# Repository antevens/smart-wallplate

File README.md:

# Smart wall plate

Replacement for a single-gang light switch: recessed IKEA BILRESA remote, hidden
emergency rocker, Apollo MSR-2 mmWave presence + SHT45 climate + a push-to-talk
microphone for Home Assistant voice, powered by a Mean Well IRM-03-5 on the wiring board.

Start with `AGENTS.md` (for people too), then `docs/SAFETY.md`. `docs/PRINTING.md` lists the print
jobs in order, `docs/ASSEMBLY.md` what holds each part, `docs/MEASUREMENTS.md` what is measured and
what is still an estimate.

Two variants: **NA** (single-gang Decora box, this page's main renders) and **EU** (round DIN 49073
box, `cad/build123d/eu/`, `pcb/eu/`). Both can run the BILRESA without batteries through a
replacement back cover powered from the plate.

The plate is two printed parts: a **box insert** (all mains/low-voltage barrier
geometry, UL94 V-0 PC-FR) and a **trim plate** (PETG/ASA), for an Elegoo Centauri
Carbon 2.

The house wiring lands on one board: L/N/PE in and out on a WAGO push-in block,
the Marquardt 1802.2504 DPST emergency rocker, and the PSU, all in a 2.5"
single-gang box. The KiCad project is in `pcb/`.

```bash
make system-deps     # once, Ubuntu 24.04 (KiCad 9, headless slicer libs)
make setup           # once (venv + pinned OrcaSlicer)
make cad check       # CAD -> build/, all checks must pass
make print           # OrcaSlicer projects -> print/*.3mf
make pcb             # all boards and flexes: ERC/DRC, STEP, PCBWay packs -> pcb/fab/, pcb/eu/fab/
make eu              # EU variant: CAD, checks, renders
make renders         # docs/renders/*.png
```

Nothing here is certified or code-compliant; see `docs/SAFETY.md`.

## How it is meant to be used

The design assumes every light bulb and device on the switched circuit is a smart
device that turns itself on and off (here IKEA Matter-over-Thread bulbs). The circuit
stays powered; day-to-day control is wireless: the BILRESA remote in the plate, Home
Assistant, the IKEA app, or Alexa / Google / other assistants.

The rocker hidden behind the remote is not the everyday light switch. It is there for
two cases:

- **Controller or cloud down.** When Home Assistant, the IKEA hub or the voice
  assistant is unavailable, turn the rocker off and on again. The bulbs restart and come
  on by themselves at their built-in power-on brightness. This needs each bulb's power-on
  behaviour set to "On" (D-8); check it per bulb.
- **Safety.** Off cuts line and neutral to the fixtures on this circuit (and powers down
  the plate's sensors), for example when a bulb or fixture misbehaves or needs changing.
  It is not a substitute for the breaker: turn the breaker off before working on any
  wiring (`docs/SAFETY.md`).

Voice: the plate's microphone streams to Home Assistant's Assist pipeline only when
listening is started from Home Assistant, for example by an automation on a BILRESA button
(D-29). There is no wake word and no speaker in the plate; replies go to another device.

Plain (non-smart) bulbs on this circuit would just follow the rocker, and the remote,
the sensors and the automations could not control them.

## Renders

### v0.3

Shaded views of the assembly: trim plate (white), box insert (grey), BILRESA
remote (model), Marquardt 1802.2504 rocker (red), wiring board (green, KiCad
model), board posts (orange). Regenerate with `make renders`.

| Front | Remote lifted out |
| --- | --- |
|  |  |

| Half-section | Back, mains side |
| --- | --- |
|  |  |

Exploded: remote, trim plate, box insert, the four board posts that screw into
the insert's bosses (D-28), wiring board (with the rocker, WAGO block and PSU from
the KiCad model).

Sensor flex (D-27, trim and remote hidden): from the MSR-2's rear connector across
the top, down the right channel past the insert, to the SHT45 on its tail.

Power contact: two spring fingers on the flex press on the gold pads of the 5 V jumper's
stiffened end, which sits on a shelf off the insert flange.

5 V power path (insert cut at the pass-through, seen from the right): a single-layer flex
jumper plugs into J2 on the wiring board (Hirose FH12-6S, slide lock), folds once between the
board and the insert (a 40 mm service loop: plug it in with the board held beside the insert,
where the latch can be seen), goes up through the pass-through and out of the flange, and ends
on the shelf under the spring fingers. No wires, no solder joints at assembly.

Face plate lifted off (trim see-through): the flex with the MSR-2, SHT45, mic and spring fingers goes
with the face plate; the 5 V jumper (wiring board J2 -> pass-through -> pad end on the shelf) stays on
the insert side. The fingers on the jumper's pads are the only electrical interface (R9, checked).

Microphone (D-29, push-to-talk voice to Home Assistant): an I²S MEMS microphone under the
flex in the right channel, its port sealed by a gasket ring to a Ø1.0 sound hole in the face
skin. Sections through the sound hole, across and along the channel:

BILRESA model: stadium outline, wheel with its gap ring, three LEDs, side
parting line, and a back that curves from a flat central pad out to the sides.

| Front | Back |
| --- | --- |
|  |  |

Cross-sections: box insert (red, UL94 V-0), trim plate (blue), wiring board
(green), board posts (orange), BILRESA (grey). The dashed line is the wall surface;
the x = -21 cut runs through two posts and their bosses.

### v0.3 wiring board

KiCad renders of `pcb/`. The front faces the plate (rocker, SMD
fuse and MOV, 5 V connector); the back faces the box (WAGO block, PSU). The four
corner holes take the insert's snap posts; they are unplated with no copper round them, and the
PE ring detours round them, so earth continuity never depends on the posts or on vias.

| Front | Back |
| --- | --- |
|  |  |
|  |  |

Without components, so every trace and pour shows:

| Front | Back |
| --- | --- |
|  |  |
|  |  |

### EU variant (concept, D-30, D-36)

A separate design for a round EU flush box (68 mm hole saw, Ø60 inside); `make eu`, `cad/build123d/eu/`,
`pcb/eu/`. The remote sits flush on a V-0 cap over the box; the emergency rocker (Marquardt 1802.2504,
as on the NA plate) under it is hidden until the remote is lifted out. Two boards: a mains board at
the rocker's PCB seat (rocker, two WAGO push-in blocks, fuse, MOV, PSU over a routed relief slot,
5 V island with a header) and a 5 V board just under the cap (pin socket on the header, two spring
pins up through the cap onto gold pads on the sensor flex: nothing soldered, wired or plugged
across). Box values are catalogue placeholders until measured; the stack reaches 43 mm deep (to be
tried in a box).

| Remote in place | Remote lifted: rocker |
| --- | --- |
|  |  |
|  |  |

Face plate lifted off: the spring pins on the 5 V board stand through the cap; the flex's pads on
the pins are the only interface (R9, checked).

| Flex | Power contact through the cap |
| --- | --- |
|  |  |

Section through the spring pins: 5 V board, pins through the cap, flex pads, trim rib behind them.

Mains board: L pours on the front, N pours on the back, the relief slot under the PSU, the 5 V island
with the header; installer labels on the back.

| Mains board, front | Mains board, back |
| --- | --- |
|  |  |
|  |  |

| 5 V board, front | 5 V board, back |
| --- | --- |
|  |  |

### Replacement back cover (D-35, D-40, D-41, D-44, D-45)

Runs the remote without cells. The printed cover snaps onto the remote like the original (clips at
the top and bottom, side ribs, a pry notch) and carries the remote's magnet plate in a clipped pocket
and a flex: two spring fingers poke through windows in its back onto flush gold pads (+5 V, GND) in a
thin pocket-floor insert, a 3.3 V regulator on the flex feeds the remote, and at the terminal end two
more fingers press on the remote's VBAT plate and GND spring. The flex is held by a stiffener and two
heat-staked pegs and, at the end, by lips and hooks on the contact blocks. On NA the floor pads come
from a tongue of the 5 V jumper through the insert above the wall plane; on EU from a tongue of the
sensor flex. No new openings in the mains barrier. Several remote dimensions are still estimates
(`docs/MEASUREMENTS.md`).

| NA, exploded: floor insert, tongue, cover, remote | NA, section on the tongue |
| --- | --- |
|  |  |

| Cover, inside | Cover, back (fingers free) |
| --- | --- |
|  |  |

| Pocket-floor insert in the EU plate | Exploded: remote, cover, floor insert, plate |
| --- | --- |
|  |  |

Cut through a finger: window, finger on the floor pad, ledge, flex. And through the VBAT contact:
the finger on the end section, its dome on the remote's battery plate.

### Sensor flex and 5 V jumper

KiCad projects in `pcb/sensor/` (D-27). The flex is drawn flat: one strip, folded twice at 45°
in the trim. Left to right: CN2 plug (placeholder, not for fabrication yet), the microphone on
its widened section (D-29), the two spring fingers over the jumper's pads, the SHT45 at the tail.

5 V jumper, drawn flat (two layers): FH12 contacts at the left, gold pads for the spring fingers at
the right (+5 V first, GND passing it to the far pad), and the battery-free tongue down to its two
floor pads.

EU sensor flex, drawn flat: CN2 plug, the microphone on its outer side, the two pads under the
spring pins, the battery-free tongue between them (folded 45° on the floor), the SHT45 at the tail.

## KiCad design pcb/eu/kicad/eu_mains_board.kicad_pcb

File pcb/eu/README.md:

# EU mains board and 5 V board (D-30, D-36)

Two boards in the round EU flush box (DIN 49073, Ø60 inside), both hanging from bosses under the
V-0 cap. Generated from `tools/eu_parts.py`, which takes its geometry from
`cad/build123d/eu/params_eu.py`.

## Mains board (`kicad/eu_mains_board.*`)

Round, at the rocker's PCB seat (16.2 mm below its panel face). The rocker breaks line and neutral
of the lights; the PSU is fed from the switched side, so the rocker also turns the sensor off.

| Ref | Part | Side | Nets |
| --- | --- | --- | --- |
| S1 | Marquardt 1802.2504 rocker, DPST, PCB pins, ENEC 12(4) A 250 V~, UL/CSA 15 A | front (through the cap's panel) | 1 L_IN, 1a L_SW, 2 N_IN, 2a N_SW |
| J1 | WAGO 2604-3102, push-in, 2-pole, 4 mm², entry 90° to the board, 400 V III/2; turned 180° from J2 | back | L_SW (pole 1), L_IN (pole 2, upper) |
| J2 | WAGO 2604-3102 (as J1) | back | N_IN (house neutral), N_SW (to the lights) |
| F1 | Schurter UMT 250, T1A 250 VAC | front | L_SW to L_F |
| RV1 | TDK CU4032K275G2, 275 VAC | front | L_F to N_SW |
| PS1 | Traco TMPS 03-105, 5 V 600 mA (IEC/UL 62368-1, IEC 60335-1; OVC II, PD2, reinforced) | back | inputs L_F / N_SW above the slot, outputs +5V / GND below it |
| J3 | Samtec TSM-102-01-L-SV, SMT pin header 1x2, 2.54 mm, 5.84 mm post (no pin tails under the PSU) | front, 5 V island | +5V, GND |
| MH1-MH3 | M2 holes on the cap's long bosses | - | - |

- The lights' current runs in copper pours: L_IN and L_SW on F.Cu (right), N_IN and N_SW on B.Cu
  (left), in above switched, as the rocker's poles; the split between them steps from the rocker's
  poles down to the WAGO block's. WAGO pin rows and body from WAGO's 3D model (8.2 mm apart, levers
  towards the board centre, where the blocks' pins stay 1.0 mm clear of the rocker body on the
  front); blocks at x ±16.6, y 7.5. The PSU feed (L_F, N_SW to F1 / RV1 / PS1) is
  1.0 mm track. Order with 2 oz copper for the load paths (sizing: human review).
- A routed relief slot under the PSU, between its input and output rows, cuts off the 5 V island
  (PSU outputs, J3). Mains copper keeps ≥ 8 mm (clearance and creepage) from it.
- Keep-out areas round the mounting holes: mains copper ≥ 1.0 mm from them.
- No PE on the board: the lights' protective earth is joined in the box (lever connector).
- Installer labels on the back: L IN / L LOAD, N IN / N LOAD at the WAGO blocks, MAINS 230 VAC.

## 5 V board (`kicad/eu_5v_board.*`)

D-shaped, just under the cap, cut below the switch cup; a hole lets the mains board's lower long
boss through. No mains on it.

| Ref | Part | Side | Nets |
| --- | --- | --- | --- |
| J1 | 2.54 mm pin socket 1x2 (8.5 mm), on the mains board's J3 | back | +5V, GND |
| C1 | 22 µF 10 V X5R 1206 | front | +5V to GND |
| P1, P2 | Harwin P70-2200045 SMT spring pins, 2 A | front | GND (P1, upper), +5V (P2) (through the cap onto the flex's pads; order set by the flex's tongue, D-42) |
| MH1, MH2 | M2 holes on the cap's bosses | - | - |

The header posts reach 3.2 mm into the socket (boards 13.8 mm apart; check with the parts).
Nothing is soldered or wired between the boards or across the cap (DESIGN R9, R10).

## Rules

`kicad/eu_mains_board.kicad_dru`: L–N ≥ 3.5 mm, any two different mains nets ≥ 3.5 mm (line / switched
line / fused line, neutral / switched neutral), mains to the 5 V side ≥ 8.0 mm (clearance and
creepage), mains to the PSU's NC pin ≥ 8.0 mm, mains copper ≥ 1.0 mm from the board edge and the
holes; pins of one rated part keep the part's own spacing. The mains pours carry their own 3.5 mm
clearance. Design targets for human review, not a compliance claim.

The net classes come from the project file; `tools/gen_eu.py` rewrites it after every save
(pcbnew's SaveBoard resets it). The single EU PSU board before D-36 was checked without them, so
its isolation was never verified by DRC.

## Regenerate

```bash
make pcb        # or pcb/eu/tools/build.sh
```

PCBWay packs for both boards in `fab/` (`fab/README.md`: order settings and the review checklist).
Order only after the review and a dry fit of the stack in a real box.

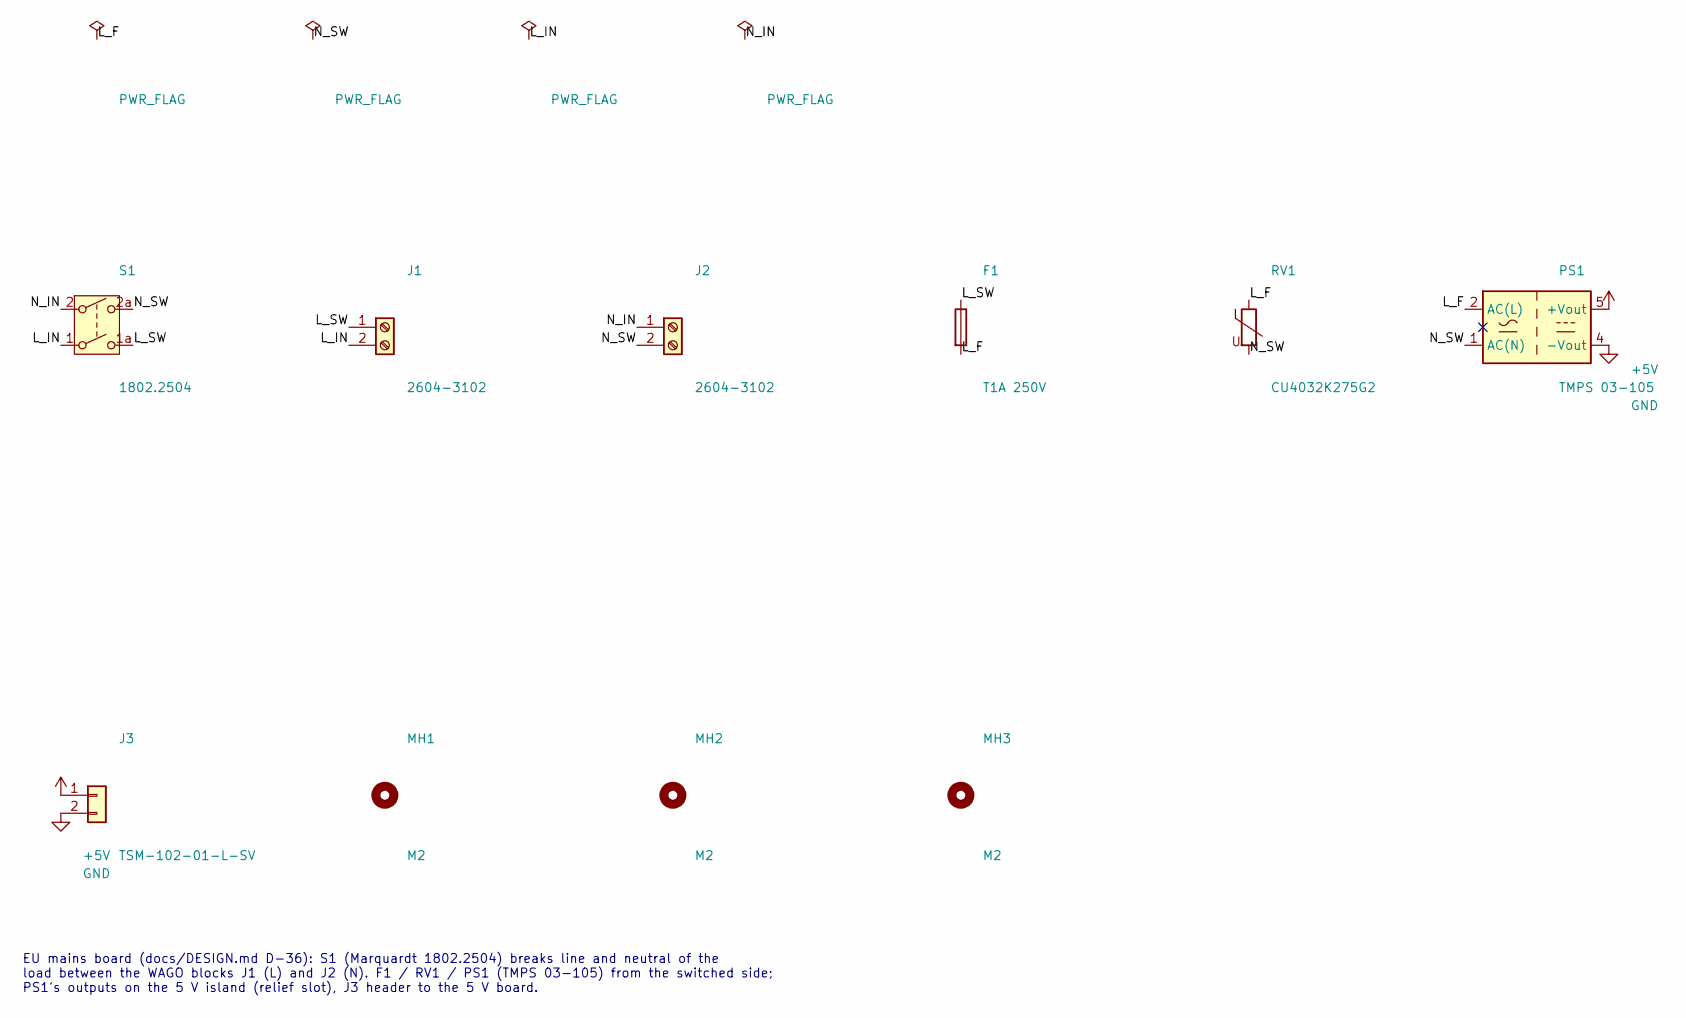
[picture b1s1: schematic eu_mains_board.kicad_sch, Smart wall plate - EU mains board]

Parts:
F1: T1A 250V; Fuse_Schurter_UMT250; MPN 3404.2416.22
J1, J2: 2604-3102; WAGO_2604-3102_1x02_P5.00mm_Vertical; MPN 2604-3102
J3: TSM-102-01-L-SV; PinHeader_1x02_P2.54mm_Vertical_SMD_Pin1Left; MPN TSM-102-01-L-SV
MH1, MH2, MH3: M2; MountingHole_2.2mm_M2
PS1: TMPS 03-105; Converter_ACDC_TRACO_TMPS03_THT; MPN TMPS 03-105
RV1: CU4032K275G2; Varistor_TDK_CU4032; MPN B72660M0271K093
S1: 1802.2504; Marquardt_1802.2504_DPST_PCB; MPN 1802.2504

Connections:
+5V: J3.1, PS1.5 (+Vout)
/L_F: F1.2, PS1.2 (AC(L)), RV1.1
/L_IN: J1.2, S1.1
/L_SW: F1.1, J1.1, S1.1a (2)
/N_IN: J2.1, S1.2 (3)
/N_SW: J2.2, PS1.1 (AC(N)), RV1.2, S1.2a (4)
GND: J3.2, PS1.4 (-Vout)

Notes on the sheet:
EU mains board (docs/DESIGN.md D-36): S1 (Marquardt 1802.2504) breaks line and neutral of the load between the WAGO blocks J1 (L) and J2 (N). F1 / RV1 / PS1 (TMPS 03-105) from the switched side; PS1's outputs on the 5 V island (relief slot), J3 header to the 5 V board.

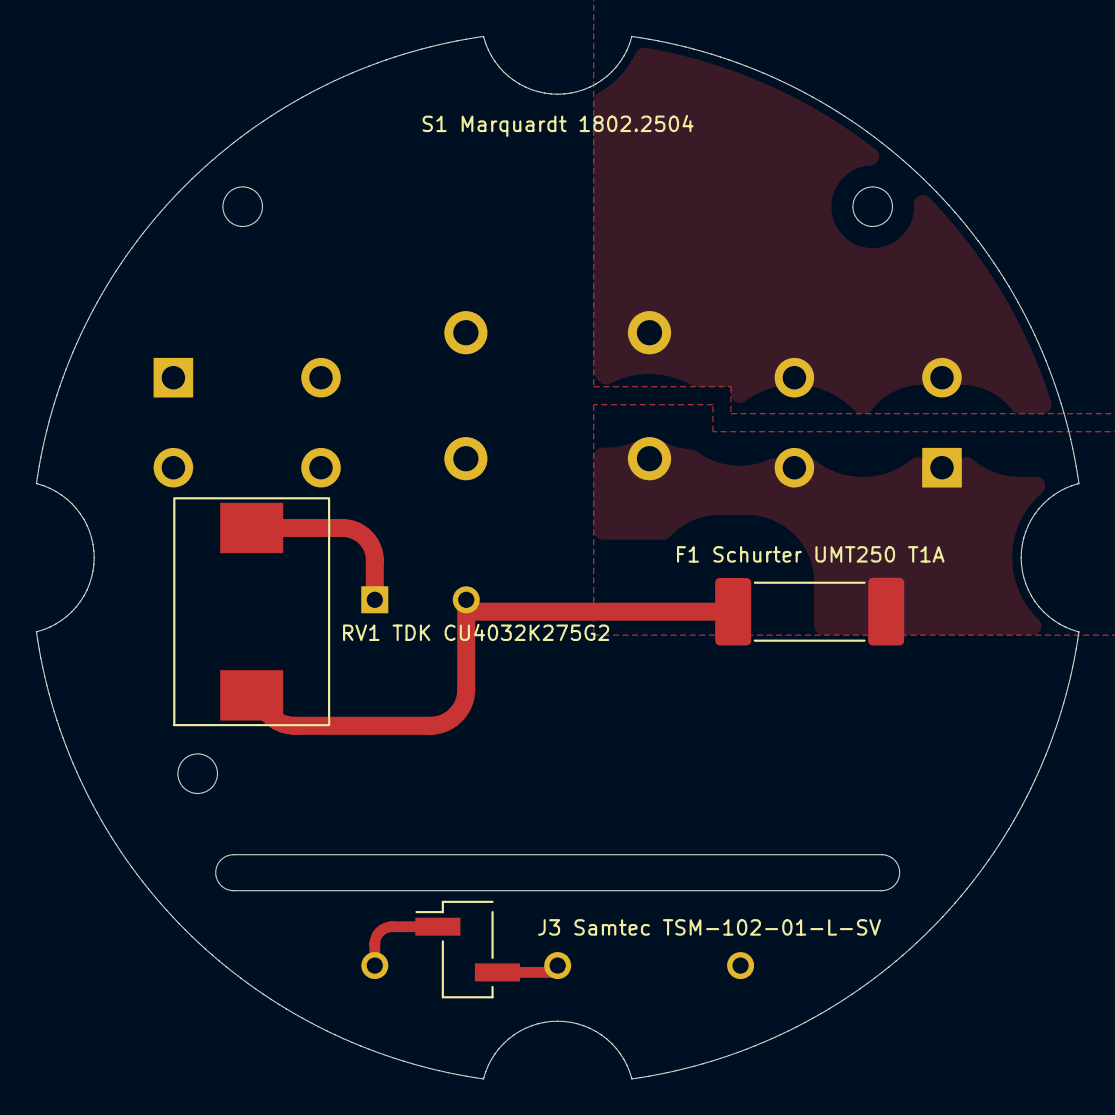
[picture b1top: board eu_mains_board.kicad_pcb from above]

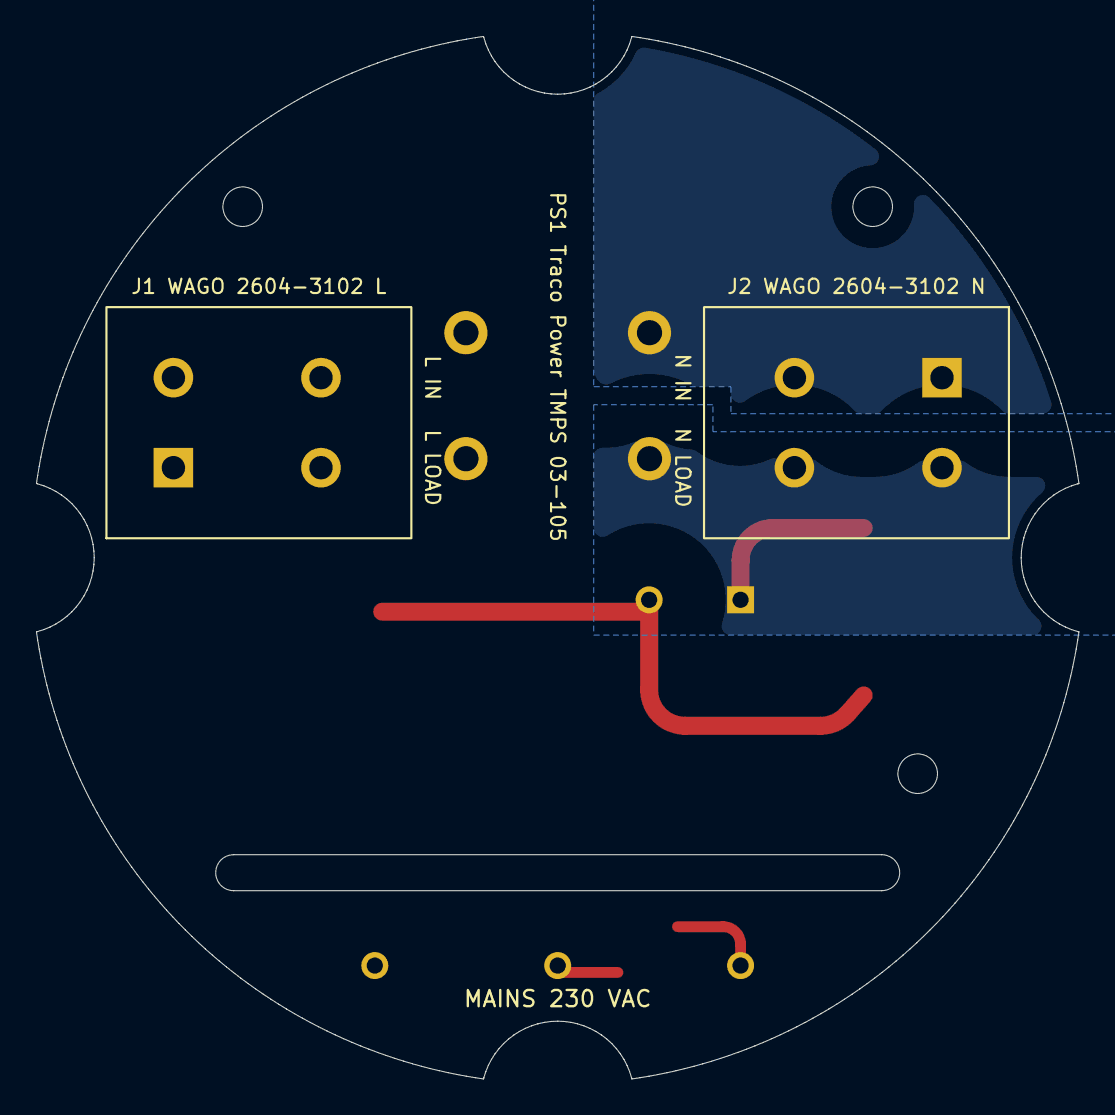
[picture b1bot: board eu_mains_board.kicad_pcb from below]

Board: 2 copper layers, 57.9 x 57.9 mm, 10 parts (3 on the bottom side), 7 nets.

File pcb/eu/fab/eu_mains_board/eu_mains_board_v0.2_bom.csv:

Item,Designator,Qty,Manufacturer,Manufacturer Part Number,Description/Value,Package/Footprint,Layer,Datasheet,Notes
1,S1,0,Marquardt,1802.2504,"1802.2504 - Rocker switch DPST, ENEC 12(4) A 250 V~, UL/CSA 15 A 125-250 VAC, PCB pins: emergency off (line and neutral of the load)",Marquardt_1802.2504_DPST_PCB,Top,"Marquardt drawing 1802.2504 rev g, 2003-09-16 (K-drawing 18022504.03)",Do not fit. Soldered by hand after the rocker is snapped into the printed cap
2,J1,1,WAGO,2604-3102,"2604-3102 - PCB terminal block, push-in, 2-pole, 4 mm2, entry 90 deg to the PCB, 400 V III/2: house line in, switched line to the load",WAGO_2604-3102_1x02_P5.00mm_Vertical,Bottom,https://www.wago.com/global/pcb-terminal-blocks-and-pluggabl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,"Safety-critical, do not substitute. Back (B) side, levers towards the board centre"
3,J2,1,WAGO,2604-3102,"2604-3102 - PCB terminal block, push-in, 2-pole, 4 mm2, entry 90 deg to the PCB, 400 V III/2: house neutral in, switched neutral to the load",WAGO_2604-3102_1x02_P5.00mm_Vertical,Bottom,https://www.wago.com/global/pcb-terminal-blocks-and-pluggabl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,"Safety-critical, do not substitute. Back (B) side, levers towards the board centre"
4,F1,1,Schurter,3404.2416.22,"T1A 250V - SMD fuse UMT 250, time-lag 1 A 250 VAC (TMPS 03 recommended input fuse T1.0 A / 250 V)",Fuse_Schurter_UMT250,Top,https://us.schurter.com/bundles/snceschurter/epim/_ProdPool_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,T1A 250 V per the Traco TMPS 03 datasheet's recommended input fuse - confirm before ordering
5,RV1,1,TDK,B72660M0271K093,"CU4032K275G2 - SMD varistor SIOV-CU4032K275G2K1, 275 VAC",Varistor_TDK_CU4032,Top,https://www.farnell.com/datasheets/2921094.pdf,"Safety-critical, do not substitute without review"
6,PS1,1,Traco Power,TMPS 03-105,"TMPS 03-105 - AC-DC module 85-264 VAC in, 5 V 600 mA, 25.4x25.4x16.3 mm, IEC/UL 62368-1, IEC 60335-1",Converter_ACDC_TRACO_TMPS03_THT,Bottom,https://www.tracopower.com/sites/default/files/products/data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,"Safety-critical, do not substitute. Back (B) side over the routed relief slot, sit flush"
7,J3,1,Samtec,TSM-102-01-L-SV,"TSM-102-01-L-SV - SMT pin header 1x2, 2.54 mm, 5.84 mm post, gold on post: 5 V to the 5 V board's pin socket (5 V island)",PinHeader_1x02_P2.54mm_Vertical_SMD_Pin1Left,Top,https://suddendocs.samtec.com/catalog_english/tsm.pdf,SMT header on the 5 V island (no pin tails under the PSU)

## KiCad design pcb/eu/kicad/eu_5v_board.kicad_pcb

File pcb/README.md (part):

# Wiring board (v0.3)

The single wiring board for the v0.3 plate (docs/DESIGN.md D-24, D-25, D-26). One board
carries the house wiring terminal block, the
emergency rocker that switches line and neutral, and the PSU that feeds the MSR-2.

Spacing values below are design targets for human review. Nothing here is a
compliance claim, and nothing on this board has been checked by a third party.

## Layout

Coordinates are front view in millimetres: X right, Y up toward the rocker, origin at
the board centre. F faces the plate, B faces the box.

- Board: 47 x 72 x 1.6 mm, corner radius 1.5 mm.
- Routed slot: 5 mm wide at X 3.0, from the bottom edge up to Y -10.9, under PS1.
- PE ring on both layers round the AC part, with stitching vias about every 4 mm. Earth
  continuity does not depend on vias or on copper the posts press on: on F.Cu alone, J1.6 ->
  left edge -> round MH1 -> top -> round MH3 -> J1.1 is one piece of copper, and `gen_pcb.py`
  fails the build if it is not (checked with the vias left out). The ring detours round MH1
  and MH3 on the inside; MH2 interrupts the ring's bottom-left corner (the lower part stays joined
  to both arms). B.Cu is a parallel ring joined to J1.6 by the vias.
- PE arms from the ring to J1.6 (left, F) and J1.1 (right, F and B): 10.4 mm wide, flush with
  the outer edges of the pin pair's pads (row distance 8.2 plus the 2.2 mm pad),
  ending square at the pins' centre line so the pads keep the 3.5 mm to the neighbouring
  L / N terminals.
- Pours that compete for copper have fixed priorities (line over neutral), so the fill is
  the same on every rebuild.
- 5 V area: bottom right (X 7 to 19.5, Y -33.5 to -13), GND pour on F.
- Mounting holes for the insert's snap posts (D-28), 2.6 mm, all unplated: MH1 (-21, 33.5),
  MH2 (-21, -33.5), MH3 (21, 24.77), MH4 (21, -33.5). A rule area keeps all copper 2.75 mm
  from each hole on both layers (the post's shoulder and snap head bear on bare laminate).
  Board-only footprints, not in the BOM or centroid. Mains copper keeps 1.0 mm from holes.

## Parts

| Ref | Part | MPN | Side, position | Source |
| --- | --- | --- | --- | --- |
| S1 | Marquardt rocker, DPST, PCB pins | 1802.2504 | F, (0, 19.5), turned 90 degrees | Marquardt drawing 1802.2504 rev g (K-drawing 18022504.03) |
| J1 | WAGO PCB terminal block, 6-pole, 5 mm, lever | 2604-1106 | B, pin 1 at (15.5, 8.1) and (15.5, -0.1) | <https://www.wago.com/global/pcb-terminal-blocks-and-pluggable-connectors/pcb-terminal-block/p/2604-1106> |
| PS1 | Mean Well AC-DC module, 5 V 600 mA | IRM-03-5 | B, under the slot | <https://www.meanwell.com/Upload/PDF/IRM-03/IRM-03-SPEC.PDF> |
| F1 | Schurter UMT 250 SMD fuse, T1A 250 VAC | 3404.2416.22 | F, (-14.6, -23) | <https://us.schurter.com/bundles/snceschurter/epim/_ProdPool_/newDS/en/typ_UMT_250.pdf> |
| RV1 | TDK SMD varistor 275 VAC | B72660M0271K093 (CU4032K275G2) | F, (-5.5, -22) | <https://www.farnell.com/datasheets/2921094.pdf> |
| C1 | Murata MLCC 22 uF 10 V X5R 1206 | GRM31CR61A226KE19L | F, (13, -26) | <https://www.murata.com> |
| J2 | Hirose FH12 FPC connector, 6 contacts, 0.5 mm, slide lock, 5 V out to the flex jumper | FH12-6S-0.5SH(55) | F, (13, -19.5) | <https://www.hirose.com/product/en/products/FH12/FH12-6S-0.5SH(55)/> |

S1 data from the drawing:

- Contacts 1-1a and 2-2a.
- Holes 1.3 (+0.1) mm (drilled 1.4 mm here) on a 10.2 x 7 mm grid as mounted.
- Body 22 x 18.6 mm below the panel, flange 24 x 21 mm.
- PCB seat 16.2 mm below the panel face; rocker 5.3 mm above it.
- Marked ratings: ENEC 12(4) A 250 V~; UL/CSA 15 A 125-250 VAC.
- The drawing is not in the repository.

## Nets

| Net | Class | Connects |
| --- | --- | --- |
| /L_IN | Mains_L | J1.5, S1.1 |
| /L_SW | Mains_L | J1.4, S1.1a, F1.1 |
| /L_F | Mains_L | F1.2, PS1.1 (AC/L), RV1.1 |
| /N_IN | Mains_N | J1.3, S1.2 |
| /N_SW | Mains_N | J1.2, S1.2a, PS1.3 (AC/N), RV1.2 |
| /PE | PE | J1.1, J1.6, PE ring |
| +5V | SELV | PS1.16, C1.1, J2.4–6 |
| GND | SELV | PS1.14, C1.2, J2.1–3 |

S1 pin positions (front view): L_IN (-5.1, 19.5), L_SW (-5.1, 26.5), N_IN (5.1, 19.5),
N_SW (5.1, 26.5). Pins 1 / 2 lie on the body's centre line, 1a / 2a 7 mm off it (drawing
1802.2504 rev g), so the body is centred on the in pins.

Load current path:

- Line: J1.5 to S1.1 on F, then S1.1a to J1.4 on B. The B path runs down under J1 and
  up the left edge.
- Neutral: J1.3 to S1.2 on F, then S1.2a to J1.2 on B. The B path runs up the right side.

## Rules

The rules are in `kicad/wiring_board.kicad_dru`, written by `tools/gen_project.py`.

- L to N: 3.5 mm.
- L_IN to L_SW and L_F: 3.5 mm.
- N_IN to N_SW: 3.5 mm.
- Mains to PE: 3.5 mm.
- Mains to SELV: 8.0 mm clearance and creepage, with the routed slot.
- Mains to the PSU NC pin: 8.0 mm.
- Mains copper to board edge: 1.0 mm; other copper 0.5 mm.
- Pads of one footprint keep the part's own spacing. This is the exception for
  certified parts.

Creepage is checked only for mains to SELV. On this flat board the surface path
between copper on one layer is never shorter than the straight gap, so the 3.5 mm
targets are checked as clearance. KiCad evaluates creepage rules without the
footprint, so a per-part creepage exception cannot be written.

## Status

Done:

- Generators for the libraries, the project and rules, the schematic, the board and the
  3D envelopes.
- Placement, outline and slot, PE ring with stitching vias, pours, tracks and silkscreen.
- All nets routed.
- ERC: 0 errors, 0 warnings.
- DRC (`--severity-all --schematic-parity`): 0 violations, 0 unconnected, 0 parity issues.
- STEP model in `build/wiring_board.step`; PCBWay order pack in `fab/`; renders in
  `docs/renders/wiring_board_*.png` (`make renders`).

Open:

- Meter-check the S1 pin numbering on a sample. The drawing's side view labels the
  pins 1a / 1 / 1b.
- Check the J1 pin rows on a part. They come from WAGO's 3D model (rows y 8.1 and -0.1,
  8.2 apart, D-37).
- Thermal review of the 15 A paths. The 3.5 mm targets to the neighbouring J1 pads (round,
  2.2 mm, 5 mm pitch) leave 1.6 to 1.8 mm of pour beside each pad (N_SW 1.3 mm, beside
  the PE arm) over the 2 to 3 mm where the pours leave J1. Options are 2 oz copper, or
  different targets between in and switched terminals of one pole.
- S1's body sits on the front over J1's first pin row: pad edge 1.0 mm from the body
  outline (`PAD_BODY_GAP`, checked by `make check` for every through-hole pad against the
  bodies on the other side). J1's levers overhang the S1 pins 13.9 mm or more above the
  board.
- F1 rating (T1A) is a designer's choice. Its 200 A breaking capacity at 250 VAC
  needs review against the branch circuit's prospective fault current.
- RV1 pad gap: the datasheet's D = 10.1 mm does not match B + C + B; the larger gap
  is used.
- C1 is a generic part; any 22 uF 10 V X5R 1206 fits.

## Silkscreen labels and 3D models (all boards)

Every part carries a silkscreen label with its reference and maker / model (value and size for
generic passives; net names on bare contact pads), on the side it is mounted, placed by
`tools/kigen.py` (`place_labels`): next to the part, clear of pads, other silkscreen, other parts'
courtyards and the board outline (slots included). On a single-layer flex with no room on the
copper side the label goes on the bare back. ERC / DRC (all severities) check the result.

3D models come from `tools/gen_3d.py` into each project's `kicad/3d/`: a vendor STEP from
`scratch/3d/` when present (moved into footprint coordinates by its entry), otherwise an envelope
from the datasheet dimensions. Vendor files stay in the git-ignored `scratch/` (their terms).

| Model | Source now | Vendor model |
| --- | --- | --- |
| Traco TMPS 03 | vendor (tracopower.com, 3D drawings; pins checked against the pads) | in use |
| Mean Well IRM-03, Hirose FH12-6S, Samtec TSM (EU J3), 0402 / 1206 passives | KiCad library | in use |
| Schurter UMT 250 | envelope | <https://www.schurter.com/en/datasheet/UMT%20250> |
| TDK SIOV CU4032K275G2 (B72660M0271K093) | envelope | <https://product.tdk.com/en/search/sensor/protect/varistor/info?part_no=B72660M0271K093> |
| WAGO 2604-3102 | vendor (wago.com, CADENAS; pins checked against the pads) | in use |
| WAGO 2604-1106 | vendor (wago.com, CADENAS; pins checked against the pads) | in use |
| Marquardt 1802.2504 | vendor 1802.1108 housing (Marquardt LIB_1802.1108; same 1802 flange, rocker, body) on the 1802.2504 underside from its drawing (body to 11.7, pin stems to the 16.2 seat, 0.8 pins; pins checked against the pads) | 1802.2504 itself: on request from Marquardt |
| Harwin P70-2200045 | envelope | <https://www.harwin.com/products/P70-2200045/> |
| Harwin S7081-42R | envelope (shape from the drawing) | <https://www.harwin.com/products/S7081-42R/> |
| PUI DMM-4026-B-I2S-R | envelope | <https://puiaudio.com/product/microphones/dmm-4026-b-i2s-r> |
| Sensirion SHT45 (DFN-4) | envelope | <https://sensirion.com/products/catalog/SHT45> |

To use a vendor model: put its STEP in `scratch/3d/`, add the file name and its transform to the
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
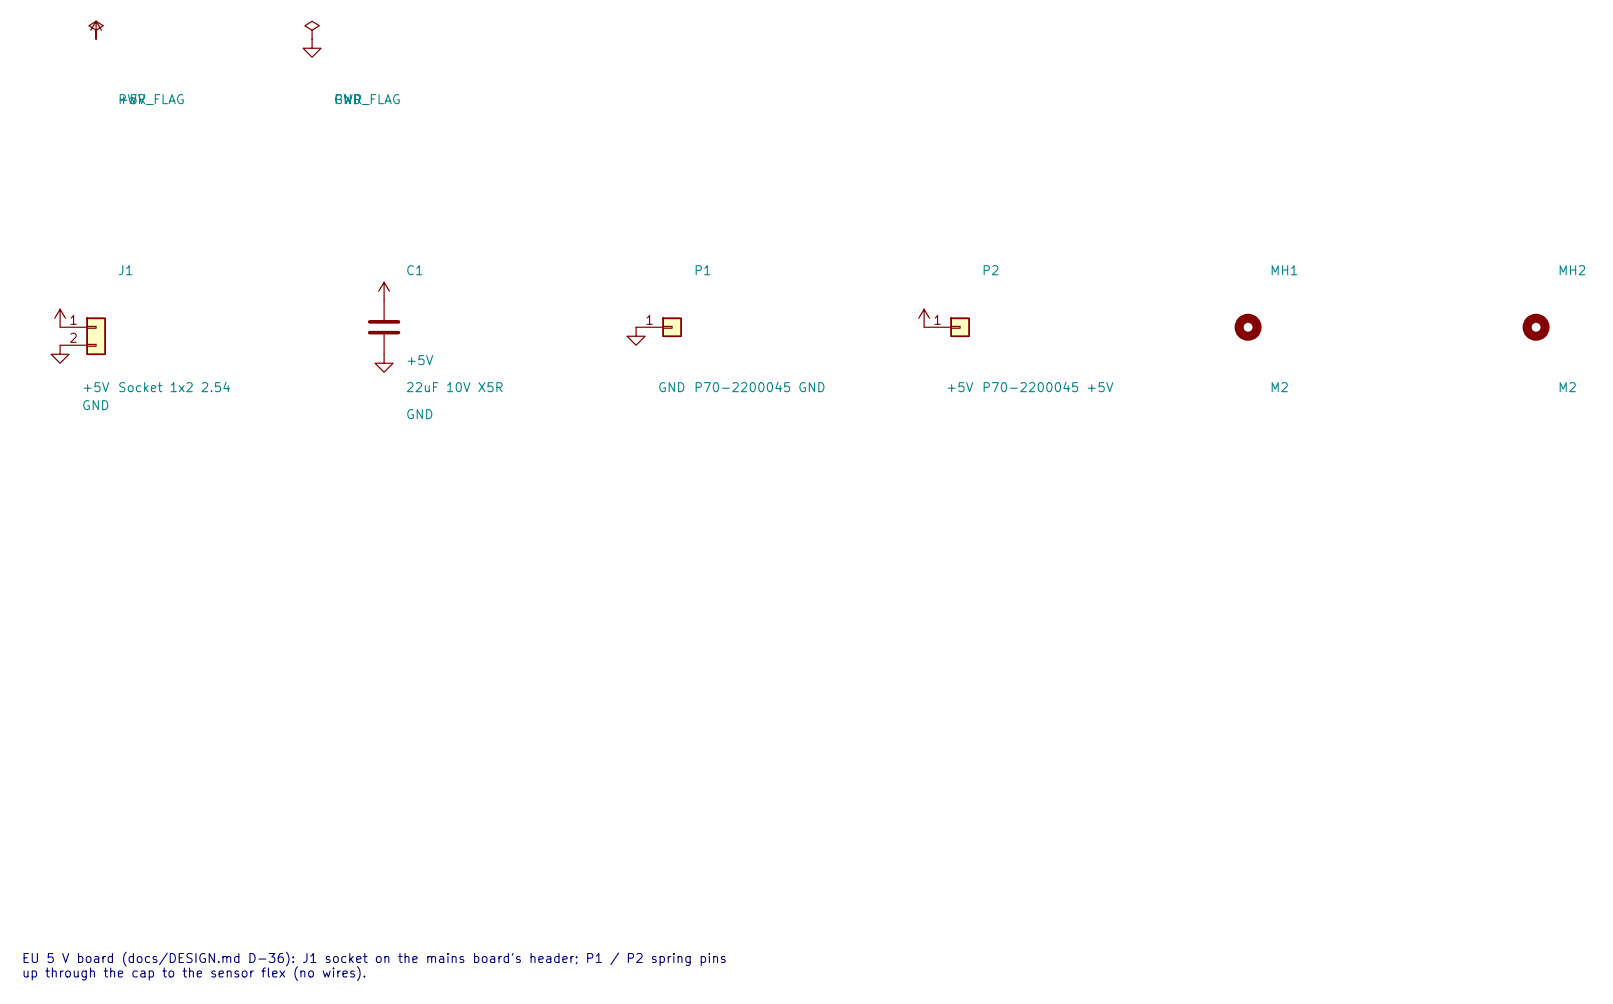
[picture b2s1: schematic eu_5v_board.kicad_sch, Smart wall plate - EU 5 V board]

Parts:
C1: 22uF 10V X5R; C_1206_3216Metric; MPN GRM31CR61A226KE19L
J1: Socket 1x2 2.54; PinSocket_1x02_P2.54mm_Vertical; MPN SSW-102-01-L-S
MH1, MH2: M2; MountingHole_2.2mm_M2
P1: P70-2200045 GND; Harwin_P70-2200045; MPN P70-2200045
P2: P70-2200045 +5V; Harwin_P70-2200045; MPN P70-2200045

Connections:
+5V: C1.1, J1.1, P2.1
GND: C1.2, J1.2, P1.1

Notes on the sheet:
EU 5 V board (docs/DESIGN.md D-36): J1 socket on the mains board's header; P1 / P2 spring pins up through the cap to the sensor flex (no wires).

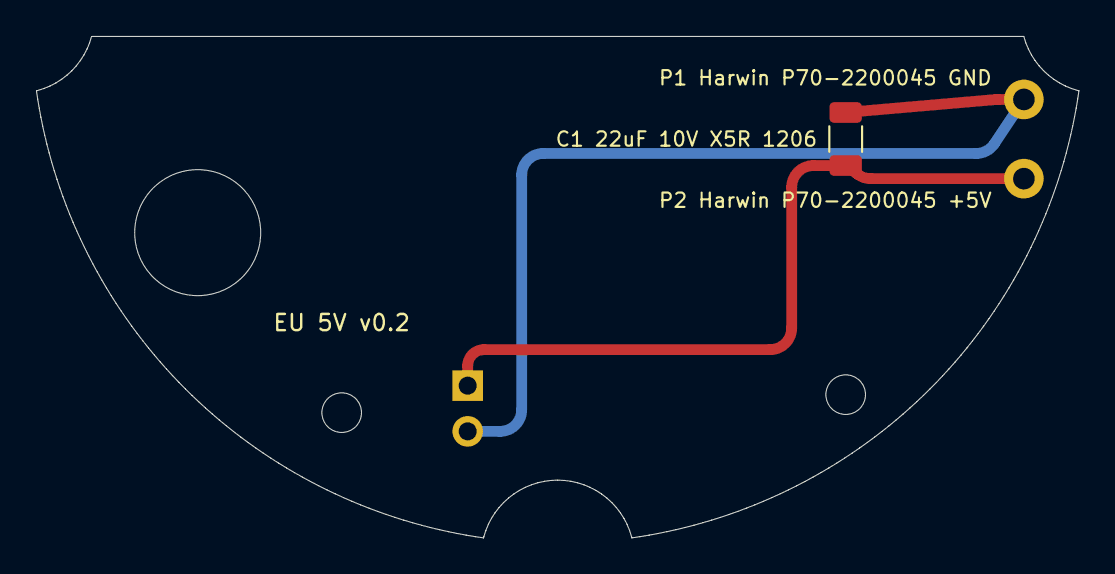
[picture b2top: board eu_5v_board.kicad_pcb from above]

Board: 2 copper layers, 57.9 x 27.9 mm, 6 parts (1 on the bottom side), 2 nets.

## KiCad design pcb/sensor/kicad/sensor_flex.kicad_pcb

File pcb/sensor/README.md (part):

# Sensor flex and 5 V jumper (D-27, D-29)

Two flex circuits on the 5 V side, generated from `tools/sensor_parts.py`, which takes its
geometry from `cad/build123d/params.py` (the same routes and shelf as the CAD models in
`cad/build123d/sensor_flex.py` and `cad/build123d/jumper.py`).

Nothing here touches mains. Both boards are low-voltage only.

## Sensor flex

Single copper layer (F.Cu; KiCad keeps an empty B.Cu), polyimide, 0.12 mm, FR4 stiffeners.

In the trim the flex runs from the MSR-2 across the top, down the right channel and along the
bottom to the SHT45. Each of the two 90° corners is a 45° fold, which turns the strip over, so
in the flat it is one straight strip about 195 mm long with every part on the copper side:

- J1: mating plug for the MSR-2's rear connector CN2 (faces the MSR-2).
- J2, J3: Harwin S7081-42R spring fingers, +5 V and GND (face the jumper's pad end).
- U1: Sensirion SHT45 with C1 (100 nF) on the tail (face the trim's vents).
- MK1: PUI Audio DMM-4026-B-I2S-R I²S microphone with C2 (100 nF) and R1 (100 kΩ SD pull-down),
  in the right channel above the fingers, port towards the face skin (D-29).

The fold lines are on `Cmts.User`, the stiffeners (behind J1, behind J2/J3 and behind MK1) on
`User.1`.

Between the plug end and the strip the flex tapers over 10 mm (`FLEX_NECK_L`), shallow enough
for the ten lanes to run in parallel; the MSR-2 bay frame's notch is sized from that outline.

Over the finger section the flex widens: towards the flange over the finger pads, and into a
1 mm recess in the trim's side wall for the four tracks that pass the pads.

Above the finger section the flex widens towards the flange (to 4.4 mm from the centre line,
room y 38–46) for the microphone. Its pins face the plug, the port end the fingers; the GND ring
(soldered all round, it seals the port) surrounds a Ø0.5 hole through flex and stiffener. On the
skin side an adhesive gasket ring (OD 2.6, ID 1.0, 0.15 mm) seals the stiffener to the face
skin around the Ø1.0 sound hole.

Nets: +5V (fingers to CN2), GND, +3V3 (CN2 to the SHT45), SDA = IO1, SCL = IO0 (MSR-2 I²C
bus; SHT45 at 0x44), I2S_SCK = IO4, I2S_WS = IO6, I2S_SD = IO7, MIC_3V3 and MIC_GND (the
microphone's own CN2 contacts, joined to +3V3 and GND on the MSR-2, so its lanes cross no
others).

## Microphone firmware (D-29)

ESPHome on the MSR-2, push-to-talk: Home Assistant starts listening (for example from a BILRESA
button automation calling the action) and the voice pipeline ends it on silence. Untested
starting point:

```yaml
i2s_audio:
  - id: i2s_mic_bus
    i2s_lrclk_pin: GPIO6
    i2s_bclk_pin: GPIO4

microphone:
  - platform: i2s_audio
    id: plate_mic
    i2s_audio_id: i2s_mic_bus
    adc_type: external
    i2s_din_pin: GPIO7
    channel: left              # LR tied to GND
    bits_per_sample: 32bit     # 24-bit data in a 32-bit word
    sample_rate: 48000         # BCLK 3.072 MHz; the mic sleeps below 2.048 MHz

voice_assistant:
  microphone: plate_mic

api:
  actions:
    - action: start_listening
      then:
        - voice_assistant.start:
    - action: stop_listening
      then:
        - voice_assistant.stop:
```

Open: whether the pipeline accepts 48 kHz from this microphone on the C3 or needs 32 kHz, and
the C3's RAM / CPU headroom next to the radar, Wi-Fi and BLE.

**Not ready to fabricate.** J1's footprint (0.4 mm, 2 x 15) and its contact map are
placeholders: CN2's part and pin map are not confirmed (D-27, `docs/MEASUREMENTS.md`). The map
in `CN2_MAP` only keeps the single-layer fan-out from crossing. `tools/build.sh` writes no flex
fab files while `CN2_CONFIRMED` is false.

## 5 V jumper

Two copper layers, polyimide, 0.2 mm (design value, confirm with the PCBWay stack-up), 156 mm long
in the flat (`params.jumper_length()` plus the two ends) plus the battery-free tongue (D-41). It replaces the 5 V lead and the target board: nothing on the 5 V path is wired or
soldered at assembly (DESIGN R9).

- J1: six exposed contacts at 0.5 mm pitch on a stiffened end (3.5 wide, 0.3 thick in total,
  `JUMPER_END`, MEASURE: check against Hirose's FPC drawing for the FH12-6S) that plugs into J2
  of the wiring board (Hirose FH12-6S-0.5SH, slide lock). Contacts 1–3 GND, 4–6 +5V, as on J2.
  Which face carries the contacts against J2's bottom contacts is to be checked on a sample.
- Run: 3.0 mm wide, +5V and GND tracks 0.5 mm (the MSR-2 draws < 0.2 A).
- TP1, TP2: gold pads (4.5 × 1.8) on the stiffened pad end (0.6 mm in total, FR4), which lies
  on the insert's shelf under the spring fingers: +5 V nearer the run, GND at the far end, its
  track passing the +5 V pad on the wall side.

Assembly: plug the connector end into J2 with the wiring board held beside the insert, where
the latch can be seen; thread the end up through the pass-through (3.5 mm end, Ø4.5 hole); fit
the board; the 40 mm service loop (`JUMPER_SERVICE`) folds between board and insert; the pad end
lies on the shelf (adhesive on its stiffener).

- Battery-free tongue (D-41): leaves the pad end's inner edge between TP1 and TP2, through a tunnel in
  the insert flange (above the wall plane), down a groove in the pocket wall and the wall into the NA
  floor insert's recess (two 90° bends, copper stays up), then a run, a down strip clear of the switch
  well's opening and the pad strip: TP3 / TP4, 7 × 4 mm gold pads (+5V, GND) under the back cover's
  fingers. GND stays on F.Cu off the edge lane; +5V leaves TP1 through a via and passes under it on
  B.Cu, which is why the jumper has two layers. Drawn flat from `sensor_parts.TONGUE_PTS`.

## Back cover flex

Single copper layer, polyimide, for the replacement back cover that powers a BILRESA E2490
without cells (`cad/build123d/backcover.py`, DESIGN D-35). Drawn flat, seen from the copper side.

- J1, J2: Harwin S7081-42R spring fingers (+3V3, GND) on the pad section, which lies copper down
  on a ledge in the cover; the fingers reach through windows onto the plate's flush floor pads
  (working height 2.0 mm).
- A 2.6 mm run (through a slot under the GND contact block) to the terminal end; one 90° bend
  (copper outside).
- J1 takes +5 V from the floor (D-41); U1 TI TLV75533PDBVR (3.3 V, SOT-23-5) with C3 / C4 1 µF on
  the section below the fingers, copper down in a recess in the cover (0.4 mm wall left), feeds VBAT.
- J3, J4: Harwin S7081-42R spring fingers (VBAT, GND) on the end section, on the cell axes, long
  axis vertical with the bend end up (the battery contacts ride down the arm's ramp as the cover
  goes on), on a 0.4 mm FR4 stiffener (back side). The end section stands 2.0 mm (the fingers'
  working height) in from the cell end plane: J3 presses the remote's fixed VBAT plate, J4 its GND
  leaf spring (finger and leaf share the travel). Between them only a band passes under the
  remote's PCB strip.

Not ready to fabricate: the positions come from the FCC internal photos (REF) or are MEASURE;
`tools/build.sh` writes no `fab/cover_flex/` while `COVER_CONFIRMED` is false.

## EU sensor flex (`kicad/eu_sensor_flex.*`, D-30, D-42)

Single copper layer, the NA topology on the EU route (`cad/build123d/eu/sensor_eu.py`), drawn flat by
`tools/eu_flex_parts.py` (X developed along the strip through the dip, Y inwards).

- J1: CN2 mate (placeholder footprint and contact map, as on the NA flex). GND comes out on two
  contacts: GND (pin pad, tongue) and GND_SHT (the SHT45), joined on the MSR-2; MIC_3V3 / MIC_GND as
  on the NA flex.
- MK1 on the strip's outer side (mic section widened outwards): WS / SCK enter the inner pad column
  from above, SD from below through the gap with R1 (100k to MIC_GND) before the body; MIC_GND /
  MIC_3V3 run under the outer column with C2 across them; GND on to the port ring.
- TP1 / TP2: Ø2.4 pads under the 5 V board's spring pins, GND first (P1), then +5V (P2); +5V and
  the SHT45 lanes step under TP1.
- Battery-free tongue (D-41): off the pad section's inner edge between TP1 and TP2 (GND from TP1,
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
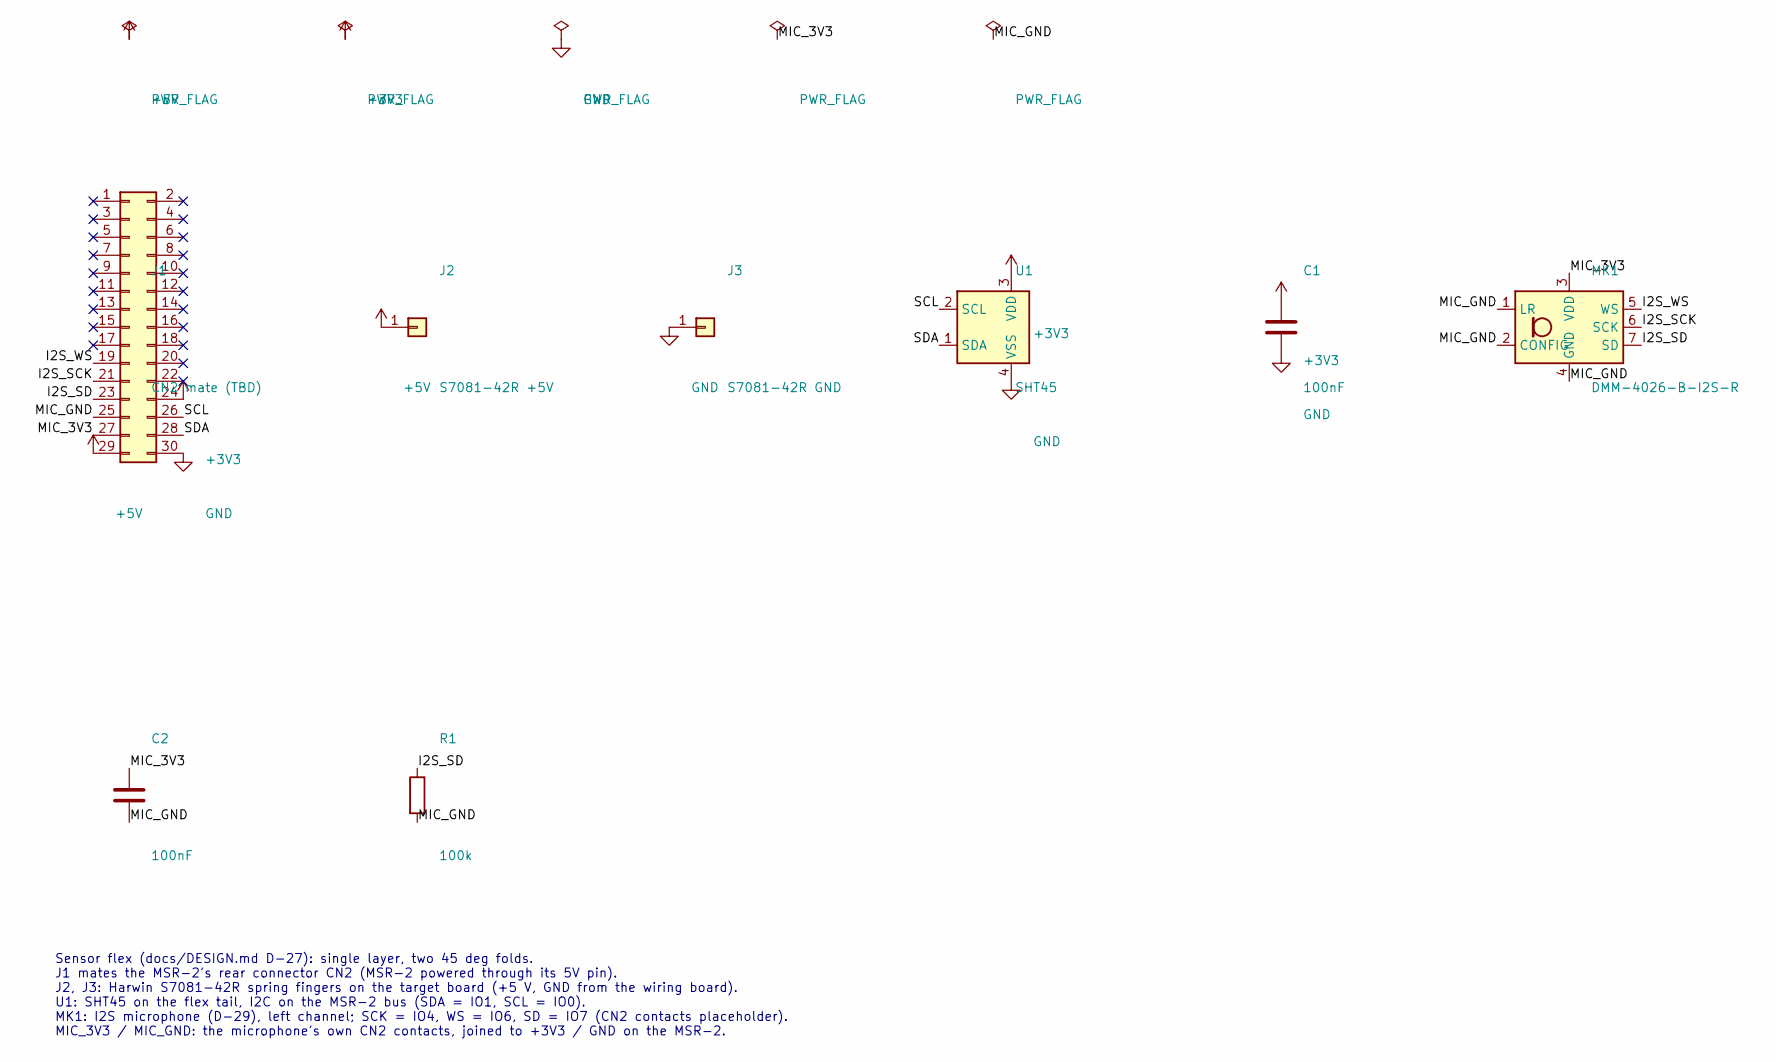
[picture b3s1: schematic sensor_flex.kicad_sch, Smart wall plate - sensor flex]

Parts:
C1, C2: 100nF; C_0402_1005Metric; MPN 0402 X7R 100 nF 16 V
J1: CN2 mate (TBD); B2B_0.4mm_2x15_PLACEHOLDER; MPN TBD
J2: S7081-42R +5V; Harwin_S7081-42R; MPN S7081-42R
J3: S7081-42R GND; Harwin_S7081-42R; MPN S7081-42R
MK1: DMM-4026-B-I2S-R; PUI_DMM-4026-B-I2S_4x3mm; MPN DMM-4026-B-I2S-R
R1: 100k; R_0402_1005Metric; MPN 0402 1% 100 kOhm
U1: SHT45; Sensirion_DFN-4_1.5x1.5mm_P0.8mm_SHT4x_NoCentralPad; MPN SHT45-AD1B-R2

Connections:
+3V3: C1.1, J1.24, U1.3 (VDD)
+5V: J1.29, J2.1
/I2S_SCK: J1.21, MK1.6 (SCK)
/I2S_SD: J1.23, MK1.7 (SD), R1.1
/I2S_WS: J1.19, MK1.5 (WS)
/MIC_3V3: C2.1, J1.27, MK1.3 (VDD)
/MIC_GND: C2.2, J1.25, MK1.1 (LR), MK1.2 (CONFIG), MK1.4 (GND), R1.2
/SCL: J1.26, U1.2 (SCL)
/SDA: J1.28, U1.1 (SDA)
GND: C1.2, J1.30, J3.1, U1.4 (VSS)

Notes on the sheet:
Sensor flex (docs/DESIGN.md D-27): single layer, two 45 deg folds. J1 mates the MSR-2's rear connector CN2 (MSR-2 powered through its 5V pin). J2, J3: Harwin S7081-42R spring fingers on the target board (+5 V, GND from the wiring board). U1: SHT45 on the flex tail, I2C on the MSR-2 bus (SDA = IO1, 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

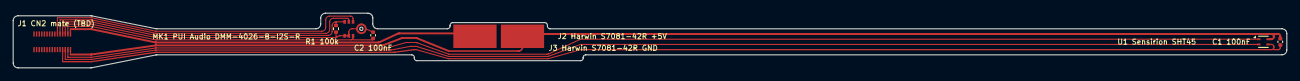
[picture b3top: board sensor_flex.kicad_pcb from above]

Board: 2 copper layers, 195.7 x 8.4 mm, 8 parts (0 on the bottom side), 10 nets.

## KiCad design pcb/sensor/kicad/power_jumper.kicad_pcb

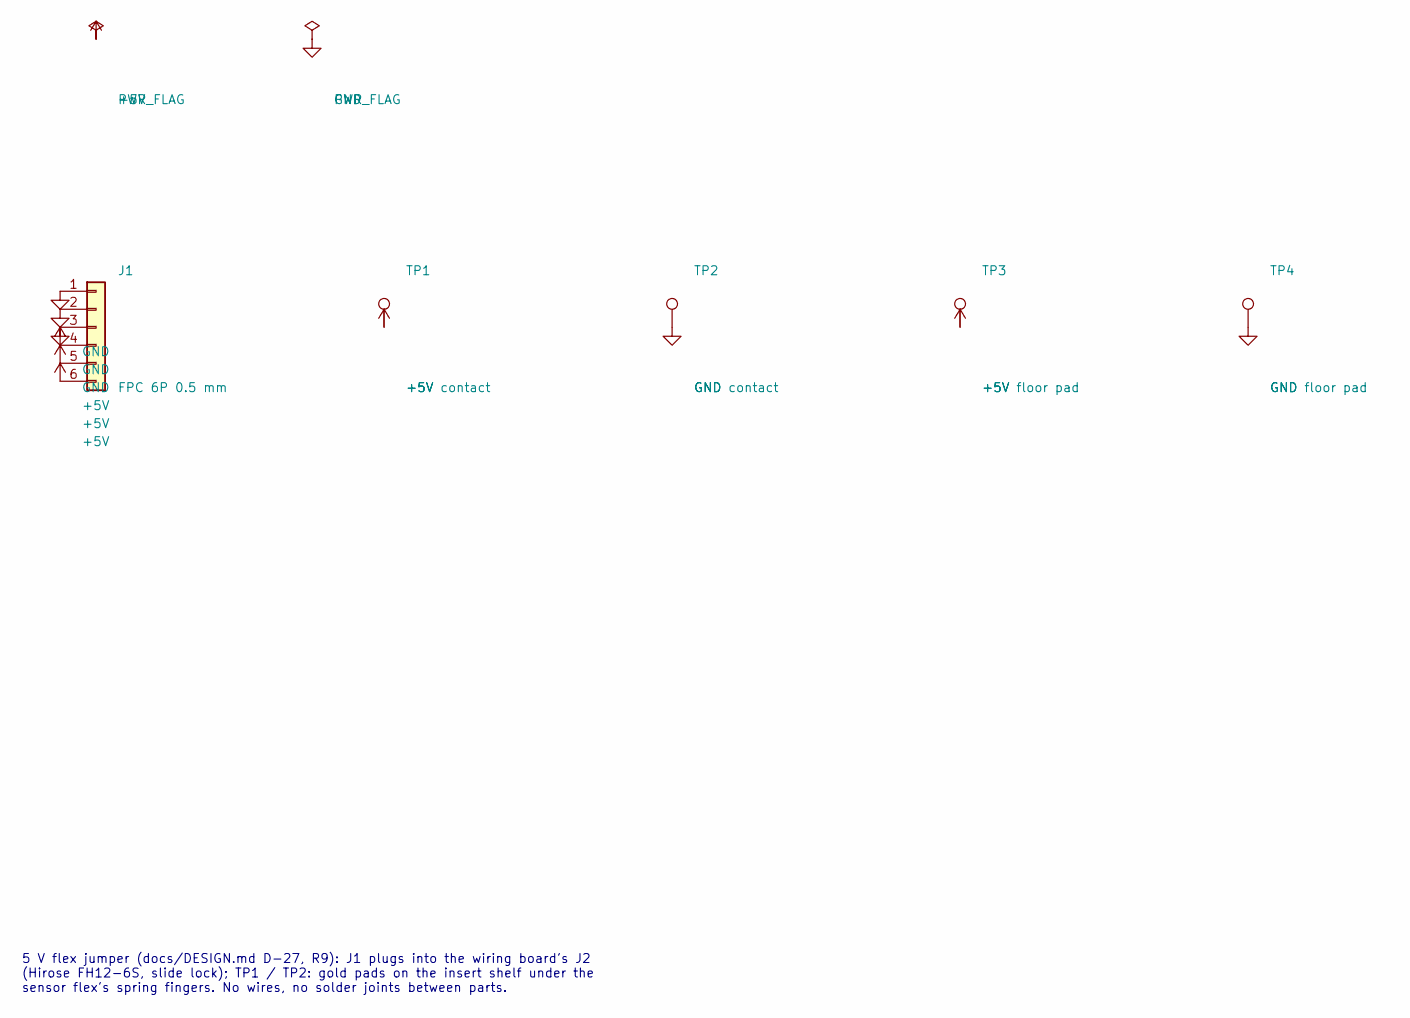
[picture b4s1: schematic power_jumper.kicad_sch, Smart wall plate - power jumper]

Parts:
J1: FPC 6P 0.5 mm; FPC_6P_P0.50mm_Contacts
TP1: +5V contact; Contact_Pad_2.2x4.5mm
TP2: GND contact; Contact_Pad_2.2x4.5mm
TP3: +5V floor pad; Contact_Pad_7x4mm
TP4: GND floor pad; Contact_Pad_7x4mm

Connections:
+5V: J1.4, J1.5, J1.6, TP1.1, TP3.1
GND: J1.1, J1.2, J1.3, TP2.1, TP4.1

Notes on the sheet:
5 V flex jumper (docs/DESIGN.md D-27, R9): J1 plugs into the wiring board's J2 (Hirose FH12-6S, slide lock); TP1 / TP2: gold pads on the insert shelf under the sensor flex's spring fingers. No wires, no solder joints between parts.

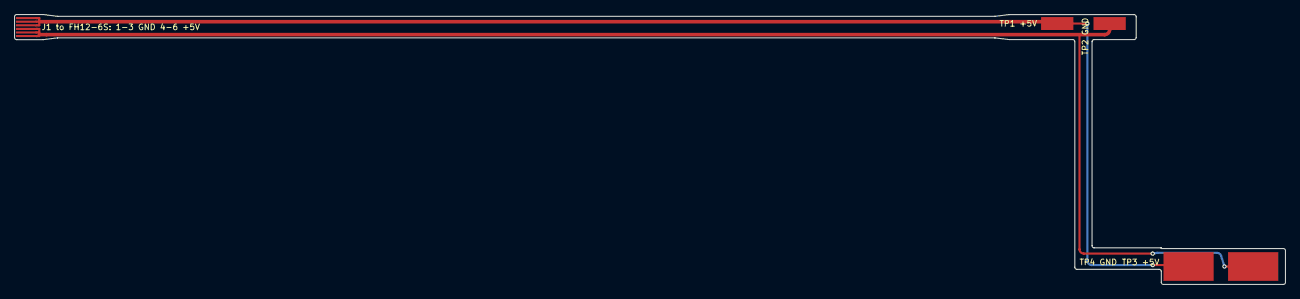
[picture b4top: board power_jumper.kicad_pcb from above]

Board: 2 copper layers, 177.1 x 37.6 mm, 5 parts (0 on the bottom side), 2 nets.
